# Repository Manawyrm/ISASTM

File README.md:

ISASTM
=============================

### Overview

ISASTM is an ISA host using a STM32H743 CPU, 32 MiB SDRAM and USB 2.0 Full-Speed / High-Speed.  
It can enable ISA cards to be used inside a VM or even emulate an x86 PC internally with an external ISA bus. 

The card is designed to be used with an ISA backplane, which supplies power and connects the ISA slots.  
The design is optimized for automated assembly at [JLCPCB](https://jlcpcb.com/DDE). 

### Errata Rev. A
- Signal integrity issues, level shifters seem to drive the bus too hard. Maybe 33R series resistance.
- Reset line is missing a pull up on the ISA bus/HV side
- USB 2.0 High speed (480 MBit/s) untested, might not work.

### Additional info

[Firmware](https://github.com/Manawyrm/ISASTM-Firmware)  
[Schematic](https://github.com/Manawyrm/ISASTM/blob/master/gerbers/RevA/ISASTM.pdf)  
  
[Twitter: Project thread](https://twitter.com/Manawyrm/status/1302558858360033280)  

### Credits
Thanks to [@Toble_Miner](https://github.com/TobleMiner) for layouting the PCB!

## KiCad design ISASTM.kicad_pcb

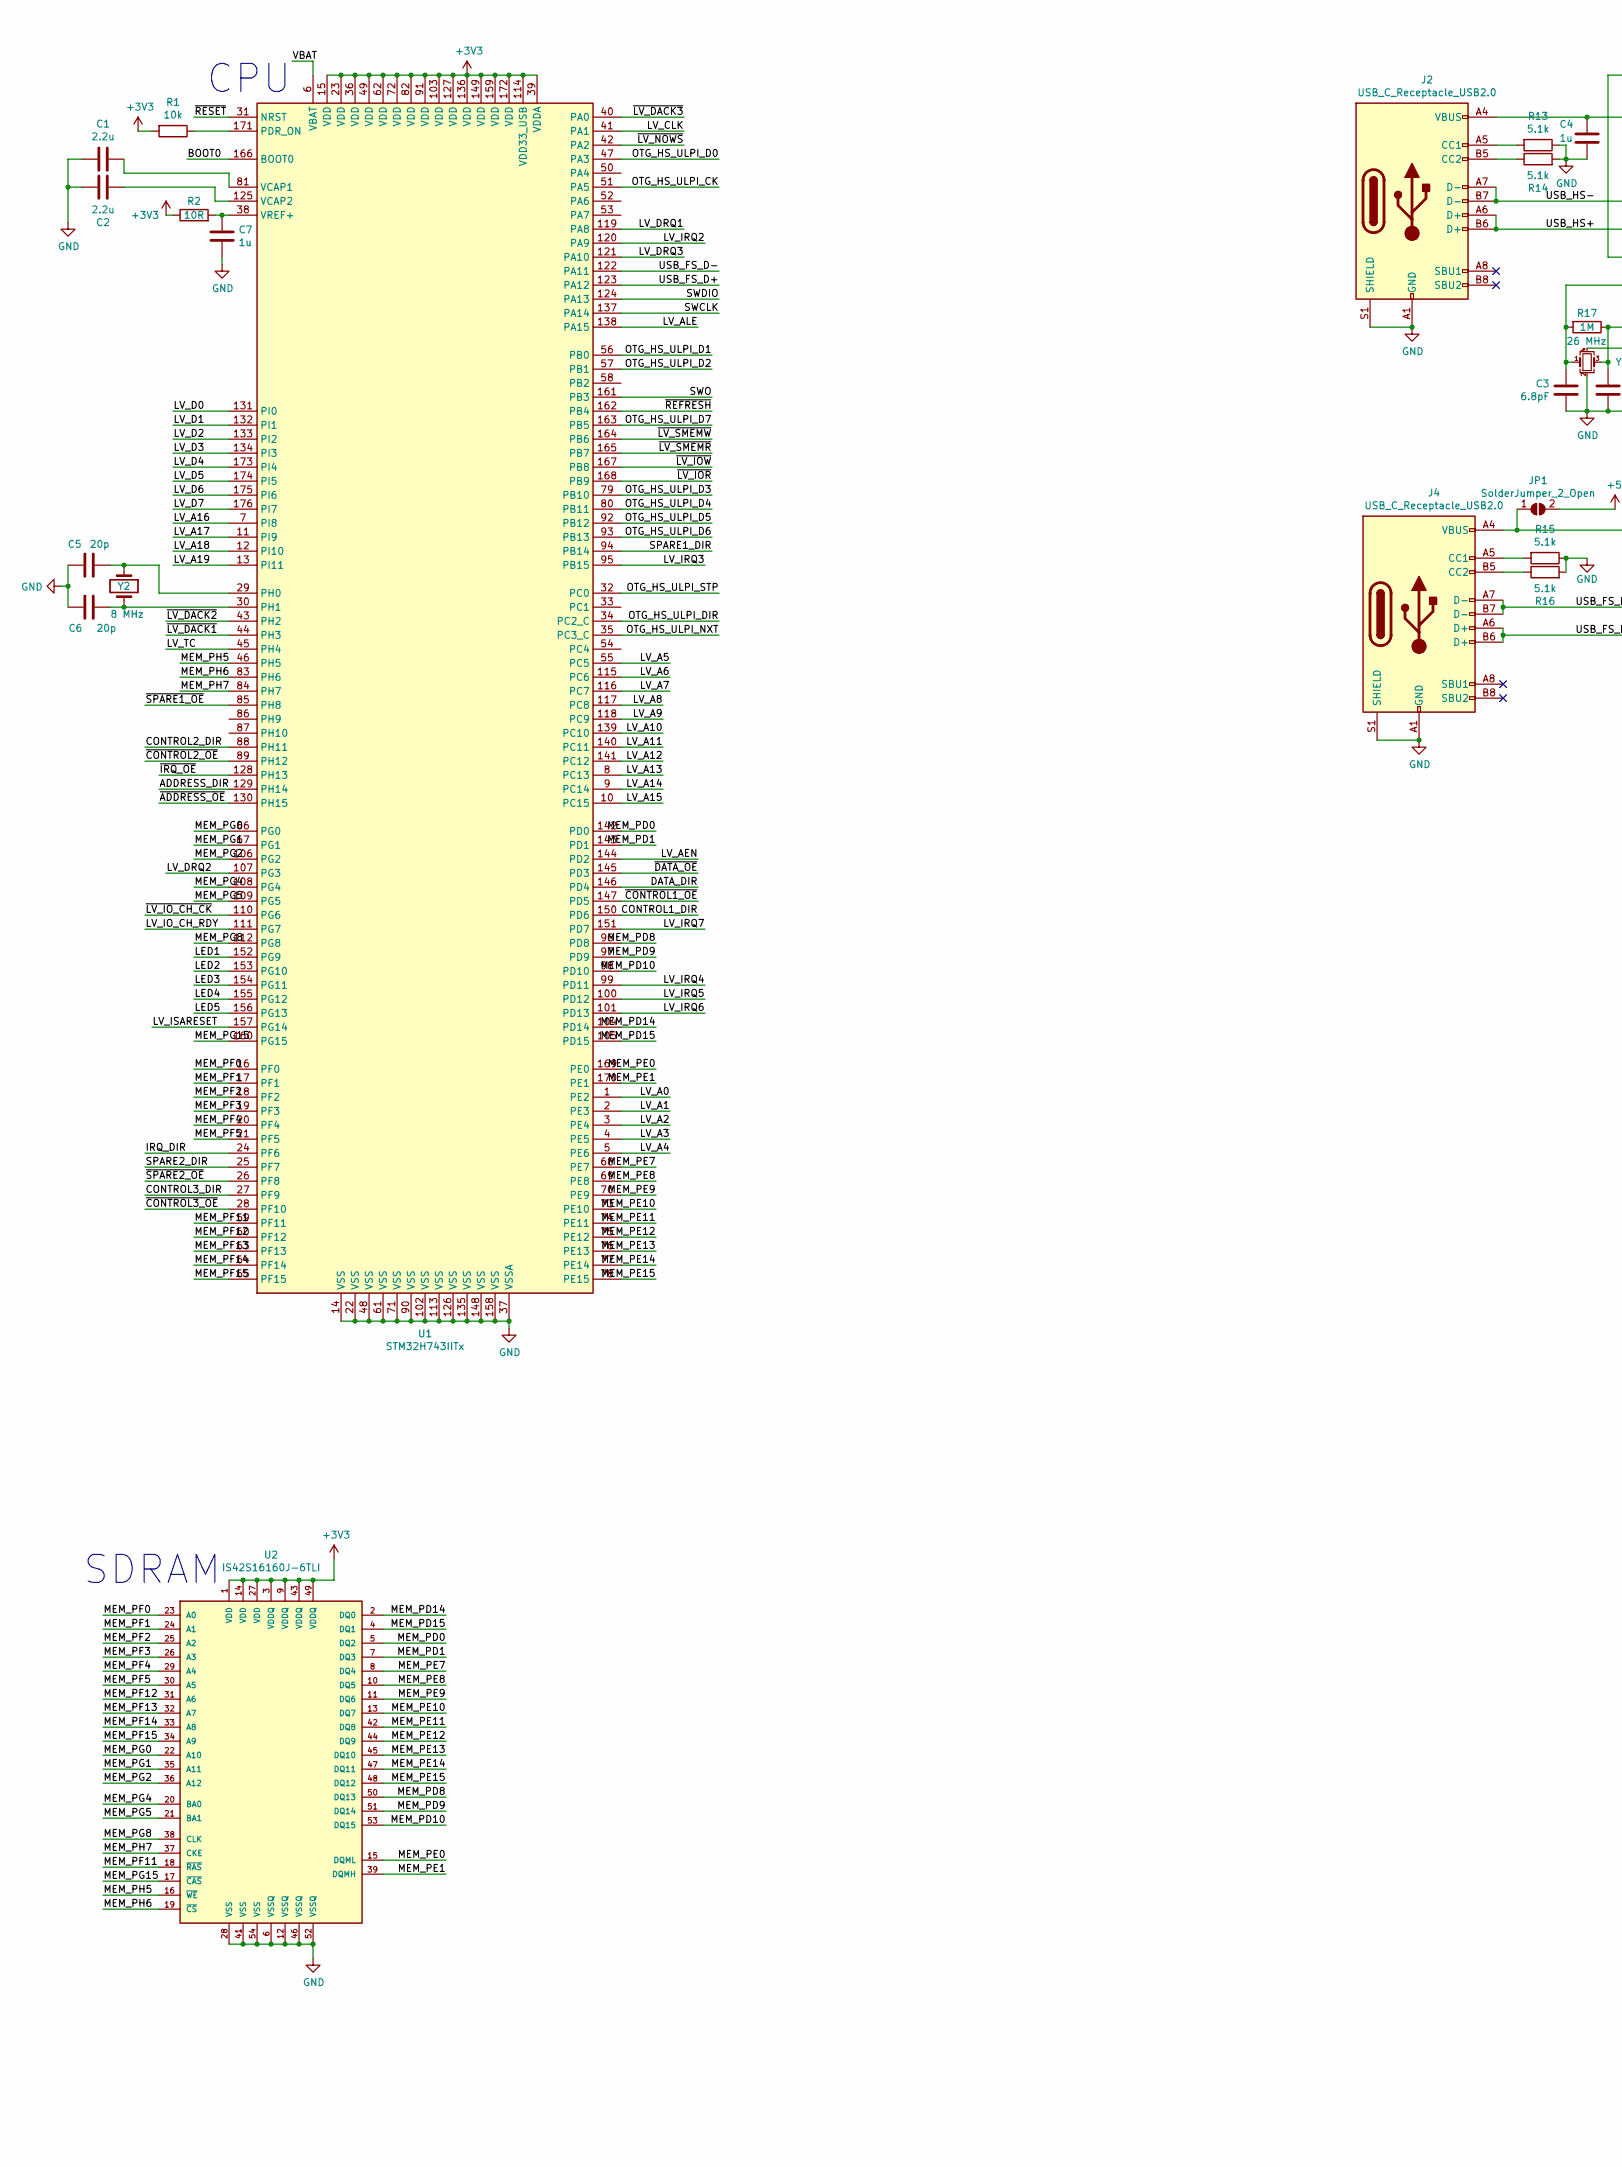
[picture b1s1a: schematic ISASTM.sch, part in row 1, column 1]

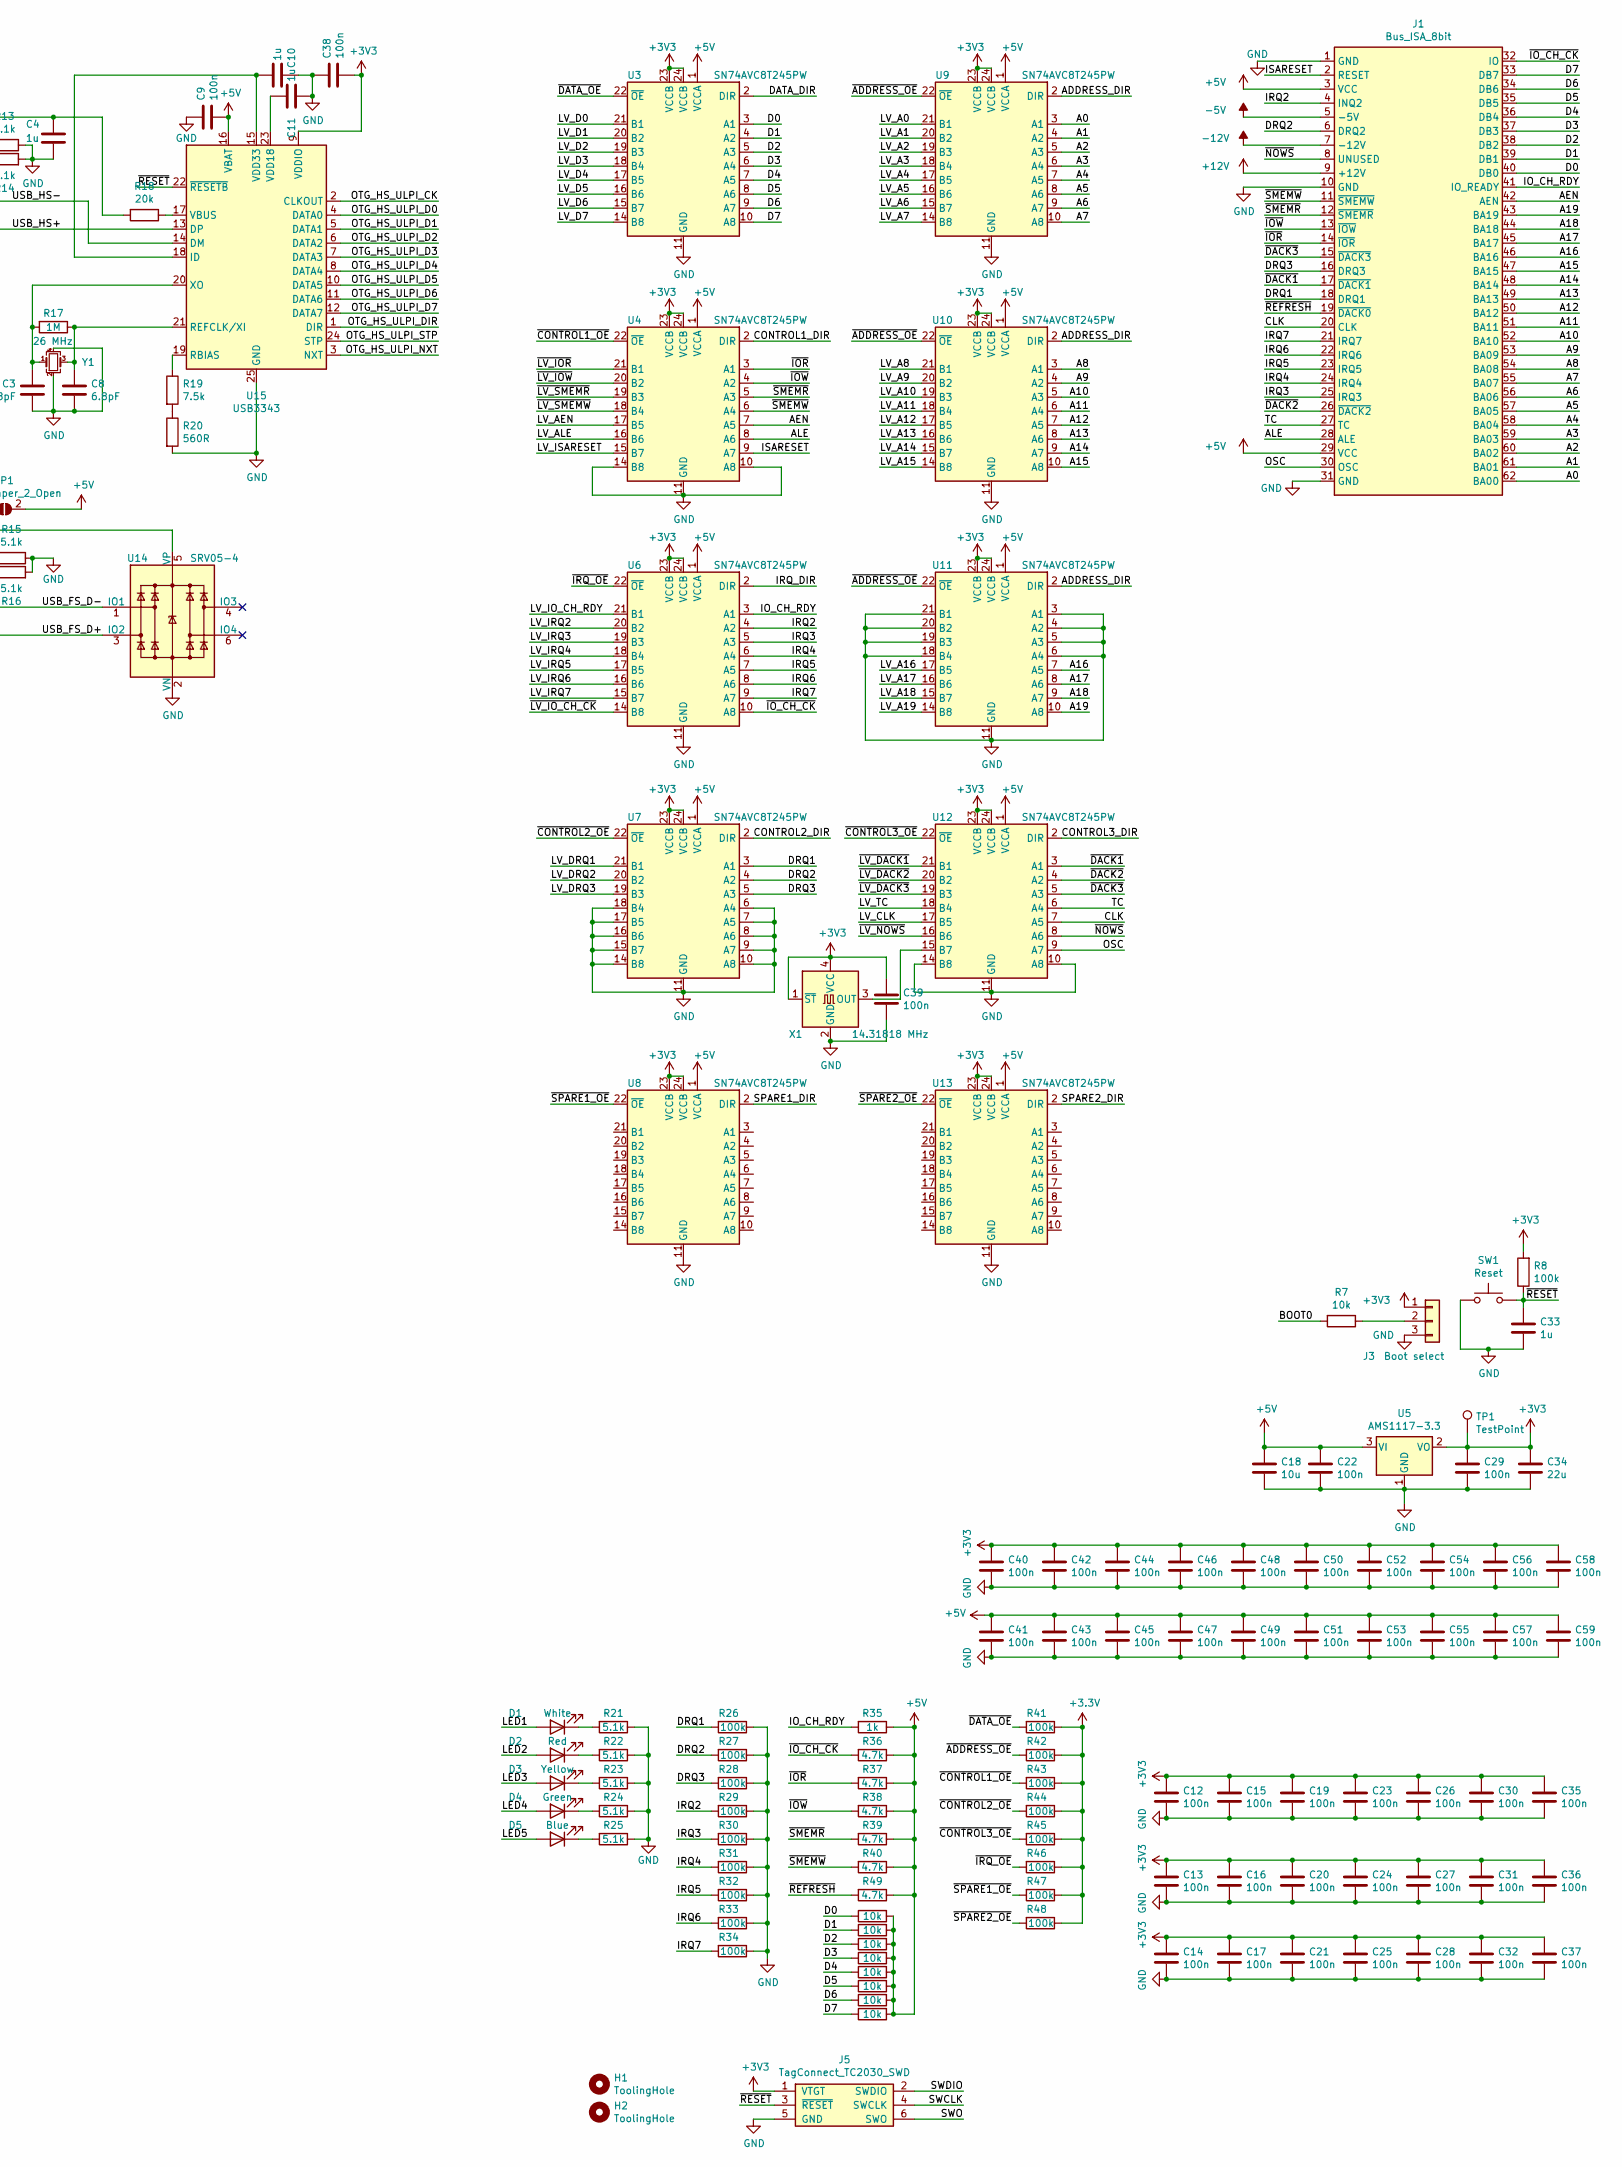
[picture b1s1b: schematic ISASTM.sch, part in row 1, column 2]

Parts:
C1, C2: 2.2u; C_0603_1608Metric; LCSC C23630
C3, C8: 6.8pF; C_0402_1005Metric; LCSC C1576
C4, C7, C10, C11, C33: 1u; C_0402_1005Metric; LCSC C52923
C5, C6: 20p; C_0402_1005Metric; LCSC C1554
C9, C12, C13, C14, C15, C16, C17, C19, C20, C21, C22, C23, C24, C25, C26, C27, C28, C29, C30, C31, C32, C35, C36, C37, C38, C39, C40, C41, C42, C43, C44, C45, C46, C47, C48, C49, C50, C51, C52, C53, C54, C55, C56, C57, C58, C59: 100n; C_0402_1005Metric; LCSC C1525
C18: 10u; C_0603_1608Metric; LCSC C19702
C34: 22u; C_0603_1608Metric; LCSC C59461
D1: White; LED_0603_1608Metric; LCSC C2290
D2: Red; LED_0603_1608Metric; LCSC C2286
D3: Yellow; LED_0603_1608Metric; LCSC C72038
D4: Green; LED_0603_1608Metric; LCSC C72043
D5: Blue; LED_0603_1608Metric; LCSC C72041
H1, H2: ToolingHole; ToolingHole_JLCSMT
J1: Bus_ISA_8bit; Conn_Edge_PCB_ISA8
J2, J4: USB_C_Receptacle_USB2.0; USB_C_Receptacle_Palconn_UTC16-G
J3: Boot select; PinHeader_1x03_P2.54mm_Vertical
J5: TagConnect_TC2030_SWD; Tag-Connect_TC2030-IDC-NL_2x03_P1.27mm_Vertical
JP1: SolderJumper_2_Open; SolderJumper-2_P1.3mm_Open_Pad1.0x1.5mm
R1, R3, R4, R5, R6, R7, R9, R10, R11, R12: 10k; R_0402_1005Metric; LCSC C25744
R2: 10R; R_0402_1005Metric; LCSC C25077
R8, R26, R27, R28, R29, R30, R31, R32, R33, R34, R41, R42, R43, R44, R45, R46, R47, R48: 100k; R_0402_1005Metric; LCSC C25741
R13, R14, R15, R16, R21, R22, R23, R24, R25: 5.1k; R_0402_1005Metric; LCSC C25905
R17: 1M; R_0402_1005Metric; LCSC C26083
R18: 20k; R_0402_1005Metric; LCSC C25765
R19: 7.5k; R_0402_1005Metric; LCSC C25918
R20: 560R; R_0603_1608Metric; LCSC C23204
R35: 1k; R_0402_1005Metric; LCSC C11702
R36, R37, R38, R39, R40, R49: 4.7k; R_0402_1005Metric; LCSC C25900
SW1: Reset; TS-1187A-X-X-X; LCSC C318887
TP1: TestPoint; TestPoint_Pad_2.0x2.0mm
U1: STM32H743IITx; LQFP-176_24x24mm_P0.5mm; LCSC C89597
U2: IS42S16160J-6TLI; TSOP-II-54_22.2x10.16mm_P0.8mm; LCSC C91278
U3, U4, U6, U7, U8, U9, U10, U11, U12, U13: SN74AVC8T245PW; TSSOP-24_4.4x7.8mm_P0.65mm; LCSC C7859
U5: AMS1117-3.3; SOT-223-3_TabPin2; LCSC C6186
U14: SRV05-4; SOT-23-6; LCSC C85364
U15: USB3343; QFN-24-1EP_4x4mm_P0.5mm_EP2.6x2.6mm
X1: 14.31818 MHz; Oscillator_SMD_SeikoEpson_SG8002CA-4Pin_7.0x5.0mm; LCSC C70517
Y1: 26 MHz; Crystal_SMD_3225-4Pin_3.2x2.5mm; LCSC C91747
Y2: 8 MHz; Crystal_SMD_5032-2Pin_5.0x3.2mm; LCSC C115962

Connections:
+5V: C9.2, C18.1, C22.1, C41.1, C43.1, C45.1, C47.1, C49.1, C51.1, C53.1, C55.1, C57.1, C59.1, J1.3 (VCC), J1.29 (VCC), JP1.2 (B), R3.2, R4.2, R5.2, R6.2, R9.2, R10.2, R11.2, R12.2, R35.1, R36.1, R37.1, R38.1, R39.1, R40.1, R49.1, U3.1 (VCCA), U4.1 (VCCA), U5.3 (VI), U6.1 (VCCA), U7.1 (VCCA), U8.1 (VCCA), U9.1 (VCCA), U10.1 (VCCA), U11.1 (VCCA), U12.1 (VCCA), U13.1 (VCCA), U15.16 (VBAT)
+12V: J1.9 (+12V)
-5V: J1.5 (-5V)
-12V: J1.7 (-12V)
/A0: J1.62 (BA00), U9.3 (A1)
/A1: J1.61 (BA01), U9.4 (A2)
/A2: J1.60 (BA02), U9.5 (A3)
/A3: J1.59 (BA03), U9.6 (A4)
/A4: J1.58 (BA04), U9.7 (A5)
/A5: J1.57 (BA05), U9.8 (A6)
/A6: J1.56 (BA06), U9.9 (A7)
/A7: J1.55 (BA07), U9.10 (A8)
/A8: J1.54 (BA08), U10.3 (A1)
/A9: J1.53 (BA09), U10.4 (A2)
/A10: J1.52 (BA10), U10.5 (A3)
/A11: J1.51 (BA11), U10.6 (A4)
/A12: J1.50 (BA12), U10.7 (A5)
/A13: J1.49 (BA13), U10.8 (A6)
/A14: J1.48 (BA14), U10.9 (A7)
/A15: J1.47 (BA15), U10.10 (A8)
/A16: J1.46 (BA16), U11.7 (A5)
/A17: J1.45 (BA17), U11.8 (A6)
/A18: J1.44 (BA18), U11.9 (A7)
/A19: J1.43 (BA19), U11.10 (A8)
/ADDRESS_DIR: U1.129 (PH14), U9.2 (DIR), U10.2 (DIR), U11.2 (DIR)
/AEN: J1.42 (AEN), U4.7 (A5)
/ALE: J1.28 (ALE), U4.8 (A6)
/BOOT0: R7.2, U1.166 (BOOT0)
/CLK: J1.20 (CLK), U12.7 (A5)
/CONTROL1_DIR: U1.150 (PD6), U4.2 (DIR)
/CONTROL2_DIR: U1.88 (PH11), U7.2 (DIR)
/CONTROL3_DIR: U1.27 (PF9), U12.2 (DIR)
/D0: J1.40 (DB0), R3.1, U3.3 (A1)
/D1: J1.39 (DB1), R4.1, U3.4 (A2)
/D2: J1.38 (DB2), R5.1, U3.5 (A3)
/D3: J1.37 (DB3), R6.1, U3.6 (A4)
/D4: J1.36 (DB4), R9.1, U3.7 (A5)
/D5: J1.35 (DB5), R10.1, U3.8 (A6)
/D6: J1.34 (DB6), R11.1, U3.9 (A7)
/D7: J1.33 (DB7), R12.1, U3.10 (A8)
/DATA_DIR: U1.146 (PD4), U3.2 (DIR)
/DRQ1: J1.18 (DRQ1), R26.2, U7.3 (A1)
/DRQ2: J1.6 (DRQ2), R27.2, U7.4 (A2)
/DRQ3: J1.16 (DRQ3), R28.2, U7.5 (A3)
/IO_CH_RDY: J1.41 (IO_READY), R35.2, U6.3 (A1)
/IRQ2: J1.4 (INQ2), R29.2, U6.4 (A2)
/IRQ3: J1.25 (IRQ3), R30.2, U6.5 (A3)
/IRQ4: J1.24 (IRQ4), R31.2, U6.6 (A4)
/IRQ5: J1.23 (IRQ5), R32.2, U6.7 (A5)
/IRQ6: J1.22 (IRQ6), R33.2, U6.8 (A6)
/IRQ7: J1.21 (IRQ7), R34.2, U6.9 (A7)
/IRQ_DIR: U1.24 (PF6), U6.2 (DIR)
/ISARESET: J1.2 (RESET), U4.9 (A7)
/LED1: D1.2 (A), U1.152 (PG9)
/LED2: D2.2 (A), U1.153 (PG10)
/LED3: D3.2 (A), U1.154 (PG11)
/LED4: D4.2 (A), U1.155 (PG12)
/LED5: D5.2 (A), U1.156 (PG13)
/LV_A0: U1.1 (PE2), U9.21 (B1)
/LV_A1: U1.2 (PE3), U9.20 (B2)
/LV_A2: U1.3 (PE4), U9.19 (B3)
/LV_A3: U1.4 (PE5), U9.18 (B4)
/LV_A4: U1.5 (PE6), U9.17 (B5)
/LV_A5: U1.55 (PC5), U9.16 (B6)
/LV_A6: U1.115 (PC6), U9.15 (B7)
/LV_A7: U1.116 (PC7), U9.14 (B8)
/LV_A8: U1.117 (PC8), U10.21 (B1)
/LV_A9: U1.118 (PC9), U10.20 (B2)
/LV_A10: U1.139 (PC10), U10.19 (B3)
/LV_A11: U1.140 (PC11), U10.18 (B4)
/LV_A12: U1.141 (PC12), U10.17 (B5)
/LV_A13: U1.8 (PC13), U10.16 (B6)
/LV_A14: U1.9 (PC14), U10.15 (B7)
/LV_A15: U1.10 (PC15), U10.14 (B8)
/LV_A16: U1.7 (PI8), U11.17 (B5)
/LV_A17: U1.11 (PI9), U11.16 (B6)
/LV_A18: U1.12 (PI10), U11.15 (B7)
/LV_A19: U1.13 (PI11), U11.14 (B8)
/LV_AEN: U1.144 (PD2), U4.17 (B5)
/LV_ALE: U1.138 (PA15), U4.16 (B6)
/LV_CLK: U1.41 (PA1), U12.17 (B5)
/LV_D0: U1.131 (PI0), U3.21 (B1)
/LV_D1: U1.132 (PI1), U3.20 (B2)
/LV_D2: U1.133 (PI2), U3.19 (B3)
/LV_D3: U1.134 (PI3), U3.18 (B4)
/LV_D4: U1.173 (PI4), U3.17 (B5)
/LV_D5: U1.174 (PI5), U3.16 (B6)
/LV_D6: U1.175 (PI6), U3.15 (B7)
/LV_D7: U1.176 (PI7), U3.14 (B8)
/LV_DRQ1: U1.119 (PA8), U7.21 (B1)
/LV_DRQ2: U1.107 (PG3), U7.20 (B2)
/LV_DRQ3: U1.121 (PA10), U7.19 (B3)
/LV_IO_CH_RDY: U1.111 (PG7), U6.21 (B1)
/LV_IRQ2: U1.120 (PA9), U6.20 (B2)
/LV_IRQ3: U1.95 (PB15), U6.19 (B3)
/LV_IRQ4: U1.99 (PD11), U6.18 (B4)
/LV_IRQ5: U1.100 (PD12), U6.17 (B5)
/LV_IRQ6: U1.101 (PD13), U6.16 (B6)
/LV_IRQ7: U1.151 (PD7), U6.15 (B7)
/LV_ISARESET: U1.157 (PG14), U4.15 (B7)
/LV_TC: U1.45 (PH4), U12.18 (B4)
/MEM_PD0: U1.142 (PD0), U2.5 (DQ2)
/MEM_PD1: U1.143 (PD1), U2.7 (DQ3)
/MEM_PD8: U1.96 (PD8), U2.50 (DQ13)
/MEM_PD9: U1.97 (PD9), U2.51 (DQ14)
/MEM_PD10: U1.98 (PD10), U2.53 (DQ15)
/MEM_PD14: U1.104 (PD14), U2.2 (DQ0)
/MEM_PD15: U1.105 (PD15), U2.4 (DQ1)
/MEM_PE0: U1.169 (PE0), U2.15 (DQML)
/MEM_PE1: U1.170 (PE1), U2.39 (DQMH)
/MEM_PE7: U1.68 (PE7), U2.8 (DQ4)
/MEM_PE8: U1.69 (PE8), U2.10 (DQ5)
/MEM_PE9: U1.70 (PE9), U2.11 (DQ6)
/MEM_PE10: U1.73 (PE10), U2.13 (DQ7)
/MEM_PE11: U1.74 (PE11), U2.42 (DQ8)
/MEM_PE12: U1.75 (PE12), U2.44 (DQ9)
/MEM_PE13: U1.76 (PE13), U2.45 (DQ10)
/MEM_PE14: U1.77 (PE14), U2.47 (DQ11)
/MEM_PE15: U1.78 (PE15), U2.48 (DQ12)
/MEM_PF0: U1.16 (PF0), U2.23 (A0)
/MEM_PF1: U1.17 (PF1), U2.24 (A1)
/MEM_PF2: U1.18 (PF2), U2.25 (A2)
/MEM_PF3: U1.19 (PF3), U2.26 (A3)
/MEM_PF4: U1.20 (PF4), U2.29 (A4)
/MEM_PF5: U1.21 (PF5), U2.30 (A5)
/MEM_PF11: U1.59 (PF11), U2.18 (~RAS~)
/MEM_PF12: U1.60 (PF12), U2.31 (A6)
/MEM_PF13: U1.63 (PF13), U2.32 (A7)
/MEM_PF14: U1.64 (PF14), U2.33 (A8)
/MEM_PF15: U1.65 (PF15), U2.34 (A9)
/MEM_PG0: U1.66 (PG0), U2.22 (A10)
/MEM_PG1: U1.67 (PG1), U2.35 (A11)
/MEM_PG2: U1.106 (PG2), U2.36 (A12)
/MEM_PG4: U1.108 (PG4), U2.20 (BA0)
/MEM_PG5: U1.109 (PG5), U2.21 (BA1)
/MEM_PG8: U1.112 (PG8), U2.38 (CLK)
/MEM_PG15: U1.160 (PG15), U2.17 (~CAS~)
/MEM_PH5: U1.46 (PH5), U2.16 (~WE~)
/MEM_PH6: U1.83 (PH6), U2.19 (~CS~)
/MEM_PH7: U1.84 (PH7), U2.37 (CKE)
/OSC: J1.30 (OSC), U12.9 (A7)
/OTG_HS_ULPI_CK: U1.51 (PA5), U15.2 (CLKOUT)
/OTG_HS_ULPI_D0: U1.47 (PA3), U15.4 (DATA0)
/OTG_HS_ULPI_D1: U1.56 (PB0), U15.5 (DATA1)
/OTG_HS_ULPI_D2: U1.57 (PB1), U15.6 (DATA2)
/OTG_HS_ULPI_D3: U1.79 (PB10), U15.7 (DATA3)
/OTG_HS_ULPI_D4: U1.80 (PB11), U15.8 (DATA4)
/OTG_HS_ULPI_D5: U1.92 (PB12), U15.10 (DATA5)
/OTG_HS_ULPI_D6: U1.93 (PB13), U15.11 (DATA6)
/OTG_HS_ULPI_D7: U1.163 (PB5), U15.12 (DATA7)
/OTG_HS_ULPI_DIR: U1.34 (PC2_C), U15.1 (DIR)
/OTG_HS_ULPI_NXT: U1.35 (PC3_C), U15.3 (NXT)
/OTG_HS_ULPI_STP: U1.32 (PC0), U15.24 (STP)
/SPARE1_DIR: U1.94 (PB14), U8.2 (DIR)
/SPARE2_DIR: U1.25 (PF7), U13.2 (DIR)
/SWCLK: J5.4 (SWCLK), U1.137 (PA14)
/SWDIO: J5.2 (SWDIO), U1.124 (PA13)
/SWO: J5.6 (SWO), U1.161 (PB3)
/TC: J1.27 (TC), U12.6 (A4)
/USB_FS_D+: J4.A6 (D+), J4.B6 (D+), U1.123 (PA12), U14.3 (IO2)
/USB_FS_D-: J4.A7 (D-), J4.B7 (D-), U1.122 (PA11), U14.1 (IO1)
/USB_HS+: J2.A6 (D+), J2.B6 (D+), U15.13 (DP)
/USB_HS-: J2.A7 (D-), J2.B7 (D-), U15.14 (DM)
/VBAT: U1.6 (VBAT)
/~ADDRESS_OE: R42.2, U1.130 (PH15), U9.22 (~OE), U10.22 (~OE), U11.22 (~OE)
/~CONTROL1_OE: R43.2, U1.147 (PD5), U4.22 (~OE)
/~CONTROL2_OE: R44.2, U1.89 (PH12), U7.22 (~OE)
/~CONTROL3_OE: R45.2, U1.28 (PF10), U12.22 (~OE)
/~DACK1: J1.17 (~DACK1), U12.3 (A1)
/~DACK2: J1.26 (~DACK2), U12.4 (A2)
/~DACK3: J1.15 (~DACK3), U12.5 (A3)
/~DATA_OE: R41.2, U1.145 (PD3), U3.22 (~OE)
/~IOR: J1.14 (~IOR), R37.2, U4.3 (A1)
/~IOW: J1.13 (~IOW), R38.2, U4.4 (A2)
/~IO_CH_CK: J1.32 (IO), R36.2, U6.10 (A8)
/~IRQ_OE: R46.2, U1.128 (PH13), U6.22 (~OE)
/~LV_DACK1: U1.44 (PH3), U12.21 (B1)
/~LV_DACK2: U1.43 (PH2), U12.20 (B2)
/~LV_DACK3: U1.40 (PA0), U12.19 (B3)
/~LV_IOR: U1.168 (PB9), U4.21 (B1)
/~LV_IOW: U1.167 (PB8), U4.20 (B2)
/~LV_IO_CH_CK: U1.110 (PG6), U6.14 (B8)
/~LV_NOWS: U1.42 (PA2), U12.16 (B6)
/~LV_SMEMR: U1.165 (PB7), U4.19 (B3)
/~LV_SMEMW: U1.164 (PB6), U4.18 (B4)
/~NOWS: J1.8 (UNUSED), U12.8 (A6)
/~REFRESH: J1.19 (~DACK0), R49.2, U1.162 (PB4)
/~RESET: C33.1, J5.3 (~RESET), R8.1, SW1.2, U1.31 (NRST), U15.22 (~RESETB)
/~SMEMR: J1.12 (~SMEMR), R39.2, U4.5 (A3)
/~SMEMW: J1.11 (~SMEMW), R40.2, U4.6 (A4)
/~SPARE1_OE: R47.2, U1.85 (PH8), U8.22 (~OE)
/~SPARE2_OE: R48.2, U1.26 (PF8), U13.22 (~OE)
GND: C1.2, C2.1, C3.2, C4.2, C5.1, C6.2, C7.2, C8.2, C9.1, C10.1, C11.1, C12.2, C13.2, C14.2, C15.2, C16.2, C17.2, C18.2, C19.2, C20.2, C21.2, C22.2, C23.2, C24.2, C25.2, C26.2, C27.2, C28.2, C29.2, C30.2, C31.2, C32.2, C33.2, C34.2, C35.2, C36.2, C37.2, C38.1, C39.2, C40.2, C41.2, C42.2, C43.2, C44.2, C45.2, C46.2, C47.2, C48.2, C49.2, C50.2, C51.2, C52.2, C53.2, C54.2, C55.2, C56.2, C57.2, C58.2, C59.2, J1.1 (GND), J1.10 (GND), J1.31 (GND), J2.A1 (GND), J2.A12 (GND), J2.B1 (GND), J2.B12 (GND), J2.S1 (SHIELD), J3.3, J4.A1 (GND), J4.A12 (GND), J4.B1 (GND), J4.B12 (GND), J4.S1 (SHIELD), J5.5 (GND), R13.1, R14.2, R15.1, R16.2, R20.2, R21.1, R22.1, R23.1, R24.1, R25.1, R26.1, R27.1, R28.1, R29.1, R30.1, R31.1, R32.1, R33.1, R34.1, SW1.1, U1.14 (VSS), U1.22 (VSS), U1.37 (VSSA), U1.48 (VSS), U1.61 (VSS), U1.71 (VSS), U1.90 (VSS), U1.102 (VSS), U1.113 (VSS), U1.126 (VSS), U1.135 (VSS), U1.148 (VSS), U1.158 (VSS), U2.6 (VSSQ), U2.12 (VSSQ), U2.28 (VSS), U2.41 (VSS), U2.46 (VSSQ), U2.52 (VSSQ), U2.54 (VSS), U3.11 (GND), U3.12 (GND), U3.13 (GND), U4.10 (A8), U4.11 (GND), U4.12 (GND), U4.13 (GND), U4.14 (B8), U5.1 (GND), U6.11 (GND), U6.12 (GND), U6.13 (GND), U7.6 (A4), U7.7 (A5), U7.8 (A6), U7.9 (A7), U7.10 (A8), U7.11 (GND), U7.12 (GND), U7.13 (GND), U7.14 (B8), U7.15 (B7), U7.16 (B6), U7.17 (B5), U7.18 (B4), U8.11 (GND), U8.12 (GND), U8.13 (GND), U9.11 (GND), U9.12 (GND), U9.13 (GND), U10.11 (GND), U10.12 (GND), U10.13 (GND), U11.3 (A1), U11.4 (A2), U11.5 (A3), U11.6 (A4), U11.11 (GND), U11.12 (GND), U11.13 (GND), U11.18 (B4), U11.19 (B3), U11.20 (B2), U11.21 (B1), U12.10 (A8), U12.11 (GND), U12.12 (GND), U12.13 (GND), U12.14 (B8), U13.11 (GND), U13.12 (GND), U13.13 (GND), U14.2 (VN), U15.25 (GND), X1.2 (GND), Y1.2, Y1.4
unnamed: C1.1, U1.81 (VCAP1)
unnamed: C2.2, U1.125 (VCAP2)
unnamed: C3.1, R17.2, U15.20 (XO), Y1.1
unnamed: C4.1, J2.A4 (VBUS), J2.A9 (VBUS), J2.B4 (VBUS), J2.B9 (VBUS), R18.2
unnamed: C5.2, U1.29 (PH0), Y2.1
unnamed: C6.1, U1.30 (PH1), Y2.2
unnamed: C7.1, R2.2, U1.38 (VREF+)
unnamed: C8.1, R17.1, U15.21 (REFCLK/XI), Y1.3
unnamed: C10.2, U15.15 (VDD33), U15.18 (ID)
unnamed: C11.2, U15.23 (VDD18)
unnamed: D1.1 (K), R21.2
unnamed: D2.1 (K), R22.2
unnamed: D3.1 (K), R23.2
unnamed: D4.1 (K), R24.2
unnamed: D5.1 (K), R25.2
unnamed: J2.A5 (CC1), R13.2
unnamed: J2.B5 (CC2), R14.1
unnamed: J3.2, R7.1
unnamed: J4.A4 (VBUS), J4.A9 (VBUS), J4.B4 (VBUS), J4.B9 (VBUS), JP1.1 (A), U14.5 (VP)
unnamed: J4.A5 (CC1), R15.2
unnamed: J4.B5 (CC2), R16.1
unnamed: R1.1, U1.171 (PDR_ON)
unnamed: R18.1, U15.17 (VBUS)
unnamed: R19.1, U15.19 (RBIAS)
unnamed: R19.2, R20.1
unnamed: U12.15 (B7), X1.3 (OUT)

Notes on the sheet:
SDRAM
CPU

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
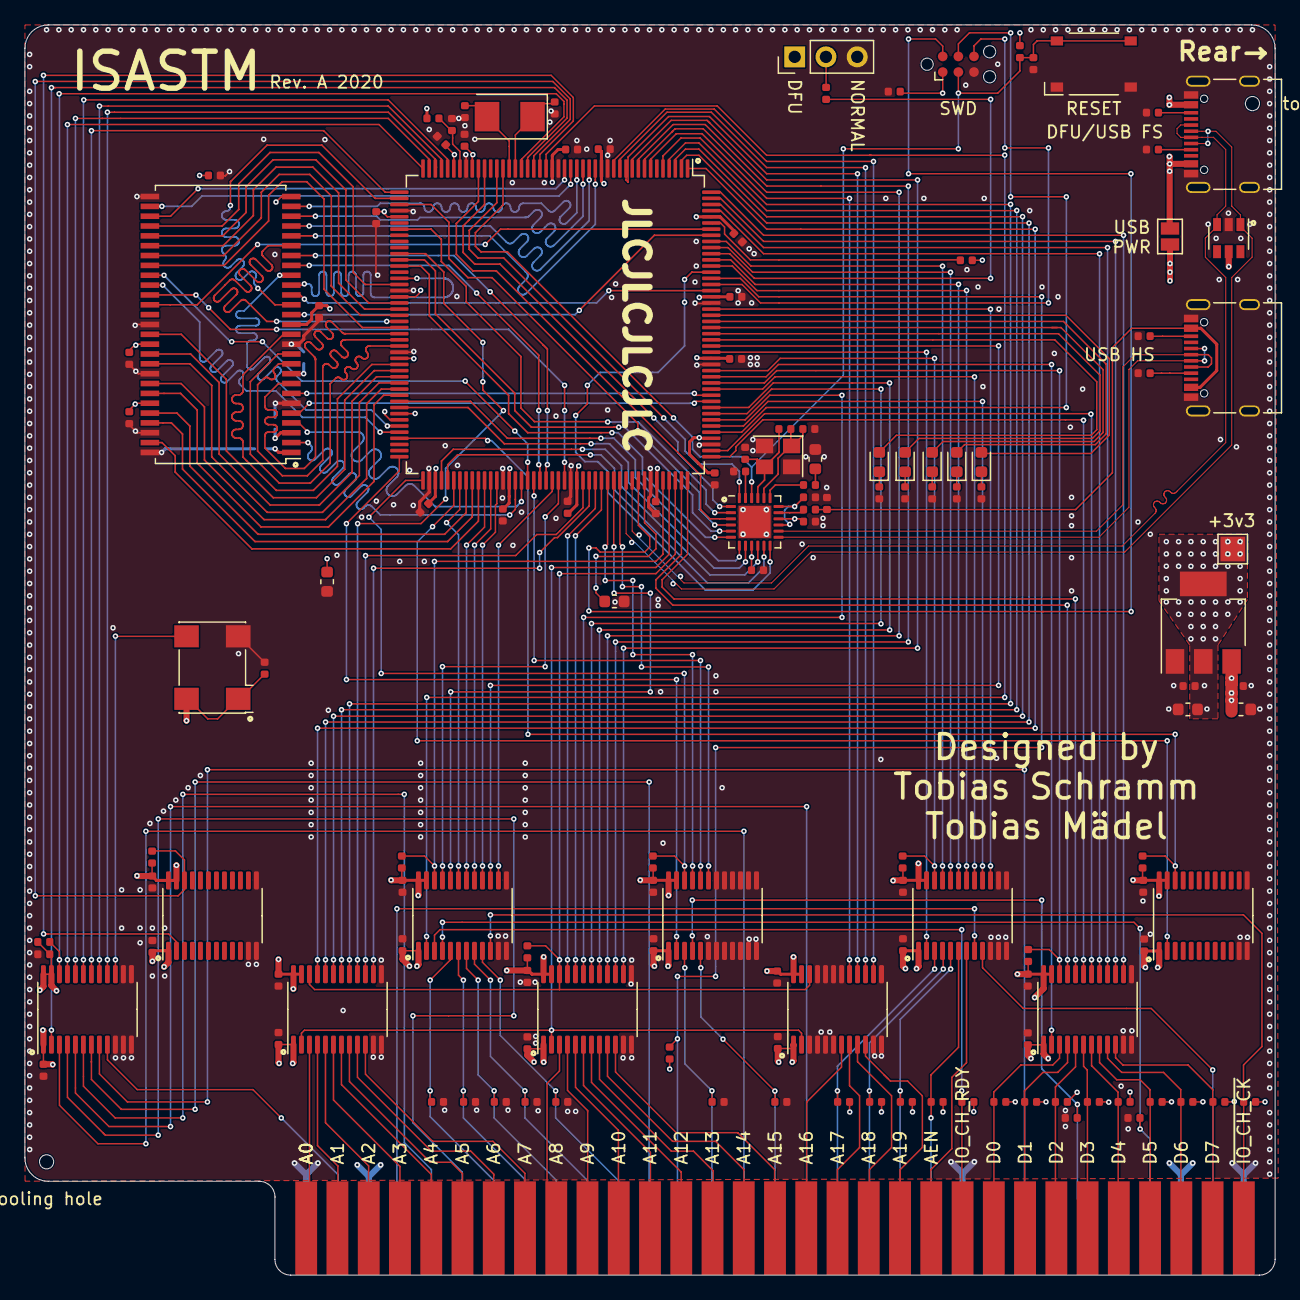
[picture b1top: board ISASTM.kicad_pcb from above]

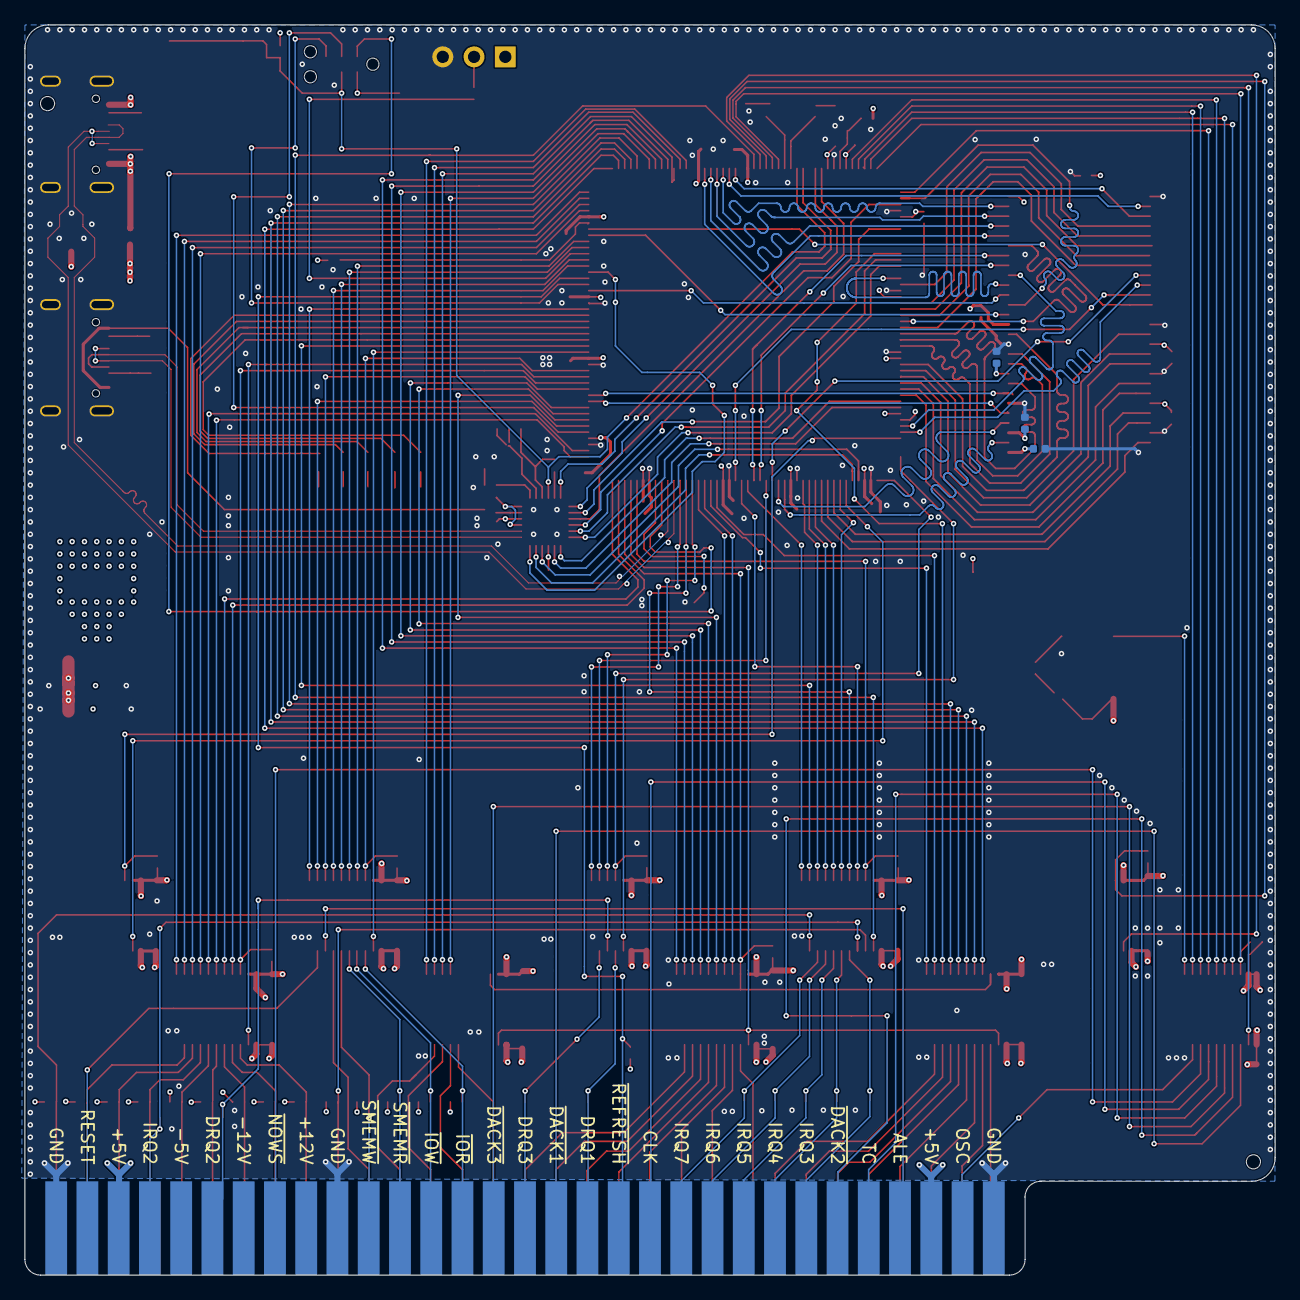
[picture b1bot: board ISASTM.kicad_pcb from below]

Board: 4 copper layers, 101.6 x 101.6 mm, 141 parts (3 on the bottom side), 216 nets.

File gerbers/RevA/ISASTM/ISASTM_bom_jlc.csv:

"Comment","Designator","Footprint","LCSC Part #"
"2.2u","C1,C2","C_0603_1608Metric","C23630"
"20p","C5,C6","C_0402_1005Metric","C1554"
"1u","C7,C33,C11,C4,C10","C_0402_1005Metric","C52923"
"6.8pF","C8,C3","C_0402_1005Metric","C1576"
"100n","C13,C16,C20,C24,C27,C29,C22,C31,C36,C14,C17,C21,C25,C28,C32,C37,C15,C19,C23,C26,C30,C35,C38,C9,C12,C39,C42,C44,C46,C48,C40,C52,C54,C56,C58,C50,C43,C45,C47,C49,C41,C53,C55,C57,C59,C51","C_0402_1005Metric","C1525"
"10u","C18","C_0603_1608Metric","C19702"
"22u","C34","C_0603_1608Metric","C59461"
"White","D1","LED_0603_1608Metric","C2290"
"Red","D2","LED_0603_1608Metric","C2286"
"Yellow","D3","LED_0603_1608Metric","C72038"
"Green","D4","LED_0603_1608Metric","C72043"
"Blue","D5","LED_0603_1608Metric","C72041"
"10k","R1,R7,R3,R4,R5,R6,R9,R10,R11,R12","R_0402_1005Metric","C25744"
"10R","R2","R_0402_1005Metric","C25077"
"100k","R8,R41,R42,R43,R44,R45,R46,R47,R48,R29,R30,R31,R32,R33,R34,R26,R27,R28","R_0402_1005Metric","C25741"
"5.1k","R13,R14,R15,R16,R21,R22,R23,R24,R25","R_0402_1005Metric","C25905"
"1M","R17","R_0402_1005Metric","C26083"
"20k","R18","R_0402_1005Metric","C25765"
"7.5k","R19","R_0402_1005Metric","C25918"
"560R","R20","R_0603_1608Metric","C23204"
"1k","R35","R_0402_1005Metric","C11702"
"4.7k","R36,R37,R38,R39,R40,R49","R_0402_1005Metric","C25900"
"Reset","SW1","TS-1187A-X-X-X","C318887"
"STM32H743IITx","U1","LQFP-176_24x24mm_P0.5mm","C89597"
"IS42S16160J-6TLI","U2","TSOP-II-54_22.2x10.16mm_P0.8mm","C91278"
"AMS1117-3.3","U5","SOT-223-3_TabPin2","C6186"
"SN74AVC8T245PW","U9,U3,U4,U10,U6,U7,U8,U13,U11,U12","TSSOP-24_4.4x7.8mm_P0.65mm","C7859"
"SRV05-4","U14","SOT-23-6","C85364"
"14.31818 MHz","X1","Oscillator_SMD_SeikoEpson_SG8002CA-4Pin_7.0x5.0mm","C70517"
"26 MHz","Y1","Crystal_SMD_3225-4Pin_3.2x2.5mm","C91747"
"8 MHz","Y2","Crystal_SMD_5032-2Pin_5.0x3.2mm","C115962"

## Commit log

2020-09-13 Add connector
2020-09-19 Add ISA bus, level shifters, memory pinout
2020-09-19 Add USB PHY, USB connectors, pull ups, DRQ/IRQ
2020-09-19 Add more decoupling
2020-09-19 Ignore logfiles
2020-09-19 Finish fanout and ULPI routing
2020-09-20 Partial ISA bus layout
2020-09-21 Route LV bus
2020-09-21 Place bias resistors
2020-09-21 Hook up ISA address + data
2020-09-21 Finish ISA signal routing
2020-09-22 Finish routing
2020-09-22 Stitch board edge
2020-09-22 Finish GND stitching
2020-09-22 Hide all footprint references
2020-09-22 Add ISA signal labels
2020-09-22 Add 3v3 testpoint
2020-09-22 Add tooling holes
2020-09-22 Match USB FS trace length
2020-09-22 Prettier silkscreen markings, aesthetic fixes for traces
2020-09-22 Add 3D model configuration, rendered pictures of RevA
2020-09-22 Fix missing ~REFRESH resistor, add better renders
2020-09-22 Add readme, schematic PDF, ibom, gerbers and change DRAM
2020-10-14 Add README
2020-10-14 Create LICENSE
